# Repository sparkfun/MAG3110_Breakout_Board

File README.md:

**NOTE:** *This product has been retired from our catalog. If you are looking for more up-to-date info, please check out some of these resources to see how other users are still hacking and improving on this product.*
* *[SparkFun Forum](https://forum.sparkfun.com/)*
* *[Comments Here on GitHub](https://github.com/sparkfun/MAG3110_Breakout_Board/issues)*

Triple Axis Magnetometer Breakout - MAG3110
============================================

__

[*Triple Axis Magnetometer Breakout - MAG3110 (SEN-12670)*](https://www.sparkfun.com/products/12670)

Breakout board for MAG3110 digital magnetometer [The datasheet can be found here.](https://dlnmh9ip6v2uc.cloudfront.net/datasheets/Sensors/Magneto/MAG3110.pdf)

This board was created in Eagle v6.5.0. 

Repository Contents
-------------------

* **/Hardware** - All Eagle design files (.brd and .sch)
* **/Libraries** - Arduino libraries
* **/Production** - Production panel files

Documentation
--------------

* **[Library](https://github.com/sparkfun/SparkFun_MAG3110_Breakout_Board_Arduino_Library)** - Arduino library 
* **[Hookup Guide](https://learn.sparkfun.com/tutorials/mag3110-magnetometer-hookup-guide-)** - Basic hookup guide 
* **[SparkFun Fritzing repo](https://github.com/sparkfun/Fritzing_Parts)** - Fritzing diagrams for SparkFun products.
* **[SparkFun 3D Model repo](https://github.com/sparkfun/3D_Models)** - 3D models of SparkFun products. 
* **[SparkFun Graphical Datasheets](https://github.com/sparkfun/Graphical_Datasheets)** -Graphical Datasheets for various SparkFun products.

Version History
---------------

* [V_H1.2](https://github.com/sparkfun/MAG3110_Breakout_Board/releases/tag/vH1.2) - Removing old libraries. Adding links to formal libs in readme.
* [V_H1.2_L1.1.0](https://github.com/sparkfun/MAG3110_Breakout_Board/releases/tag/vH1.2_L1.0)

Product Versions
---------------

* [SEN-10619](https://www.sparkfun.com/products/12670) - Version 1.2
* [SEN-10619](https://www.sparkfun.com/products/retired/10619) - Version 1.1 of the Sensor
 
License Information
-------------------
This product is _**open source**_! 

Please review the LICENSE.md file for license information. 

If you have any questions or concerns on licensing, please contact technical support on our [SparkFun forums](https://forum.sparkfun.com/viewforum.php?f=152).

Distributed as-is; no warranty is given.

- Your friends at SparkFun.

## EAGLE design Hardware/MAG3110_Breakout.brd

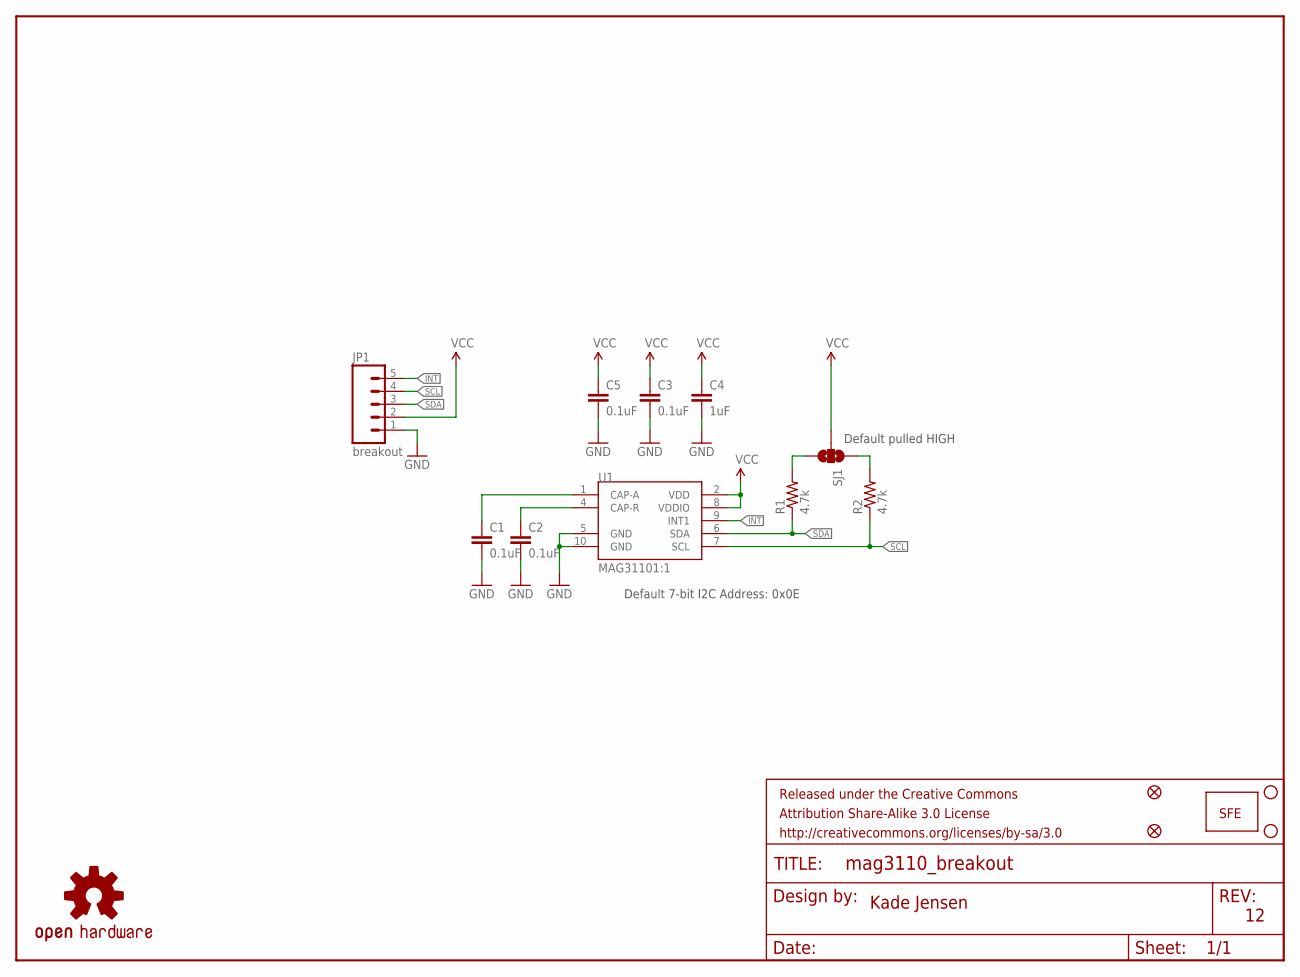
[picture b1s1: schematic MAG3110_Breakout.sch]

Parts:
C1, C2, C3, C5: 0.1uF; 0603-CAP
C4: 1uF; 0603-CAP
FID1, FID2: FIDUCIAL1X2; FIDUCIAL-1X2
FRAME2: FRAME-LETTER; CREATIVE_COMMONS
JP1: breakout; 1X05
JP2, JP3: STAND-OFF
JP7: LOGO-SFESK; SFE-LOGO-FLAME
LOGO1: OSHW-LOGOS; OSHW-LOGO-S
R1, R2: 4.7k; 0603-RES
SJ1: SOLDERJUMPER_2WAYPASTE1&2&3; SJ_3_PASTE1&2&3
U1: MAG31101:1; DFN-10-W

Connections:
GND: C1.2, C2.2, C3.2, C4.2, C5.2, JP1.1, U1.5 (GND), U1.10 (GND)
INT: JP1.5, U1.9 (INT1)
unnamed: C2.1, U1.4 (CAP-R)
unnamed: C1.1, U1.1 (CAP-A)
unnamed: R2.2, SJ1.1
unnamed: R1.2, SJ1.3
SCL: JP1.4, R2.1, U1.7 (SCL)
SDA: JP1.3, R1.1, U1.6 (SDA)
VCC: C3.1, C4.1, C5.1, JP1.2, SJ1.2, U1.2 (VDD), U1.8 (VDDIO)

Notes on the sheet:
Kade Jensen
Default pulled HIGH
Default 7-bit I2C Address: 0x0E

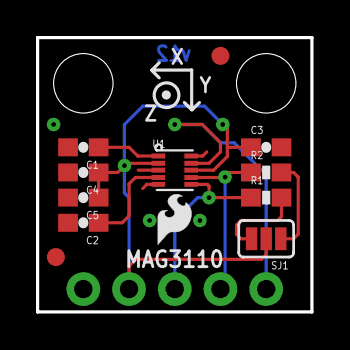
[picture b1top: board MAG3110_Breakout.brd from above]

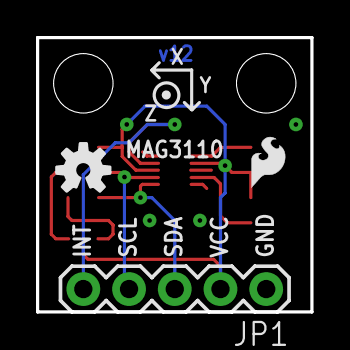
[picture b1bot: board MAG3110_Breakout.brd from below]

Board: 2 copper layers, 15.2 x 15.2 mm, 18 parts (3 on the bottom side), 9 nets.

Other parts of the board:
JP4: LOGO-SFESK; SFE-LOGO-FLAME

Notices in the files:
parts and their libraries:
SparkFun-Aesthetics: Licensing: CC v3.0 Share-Alike You are welcome to use this library for commercial purposes.
SparkFun-Aesthetics: Released under the Creative Commons Attribution Share-Alike 3.0 License
SparkFun-Aesthetics: http://creativecommons.org/licenses/by-sa/3.0
